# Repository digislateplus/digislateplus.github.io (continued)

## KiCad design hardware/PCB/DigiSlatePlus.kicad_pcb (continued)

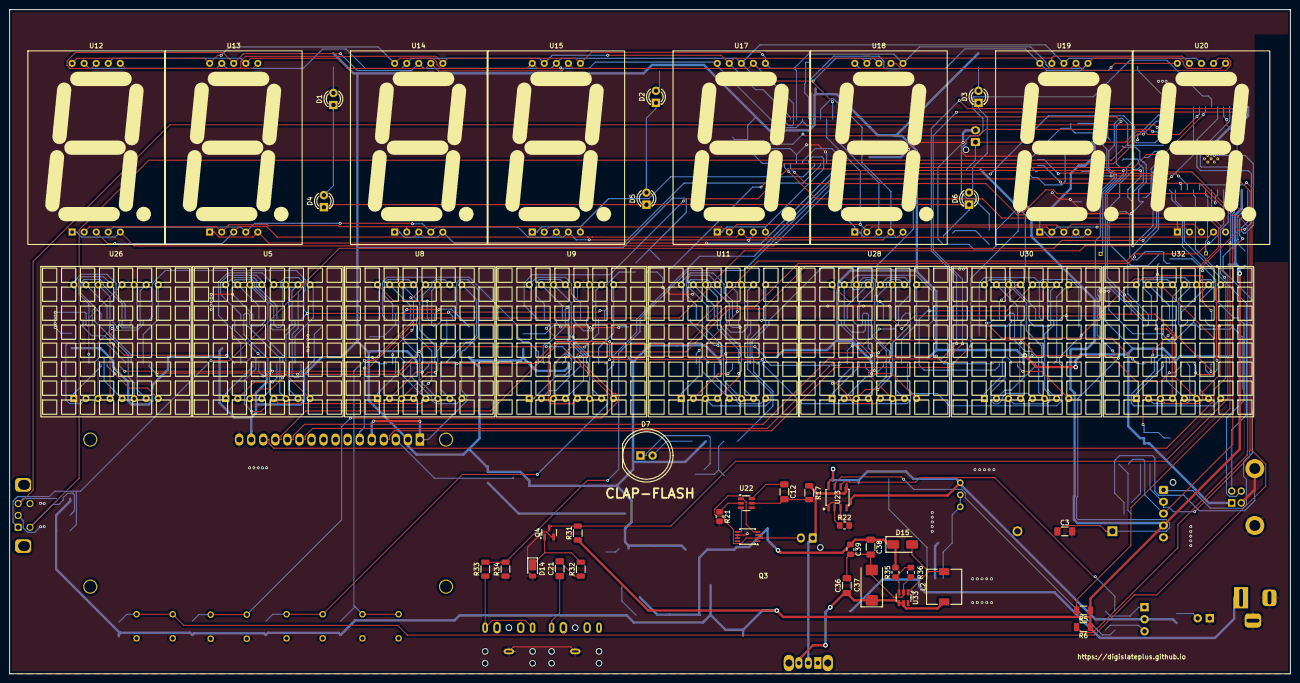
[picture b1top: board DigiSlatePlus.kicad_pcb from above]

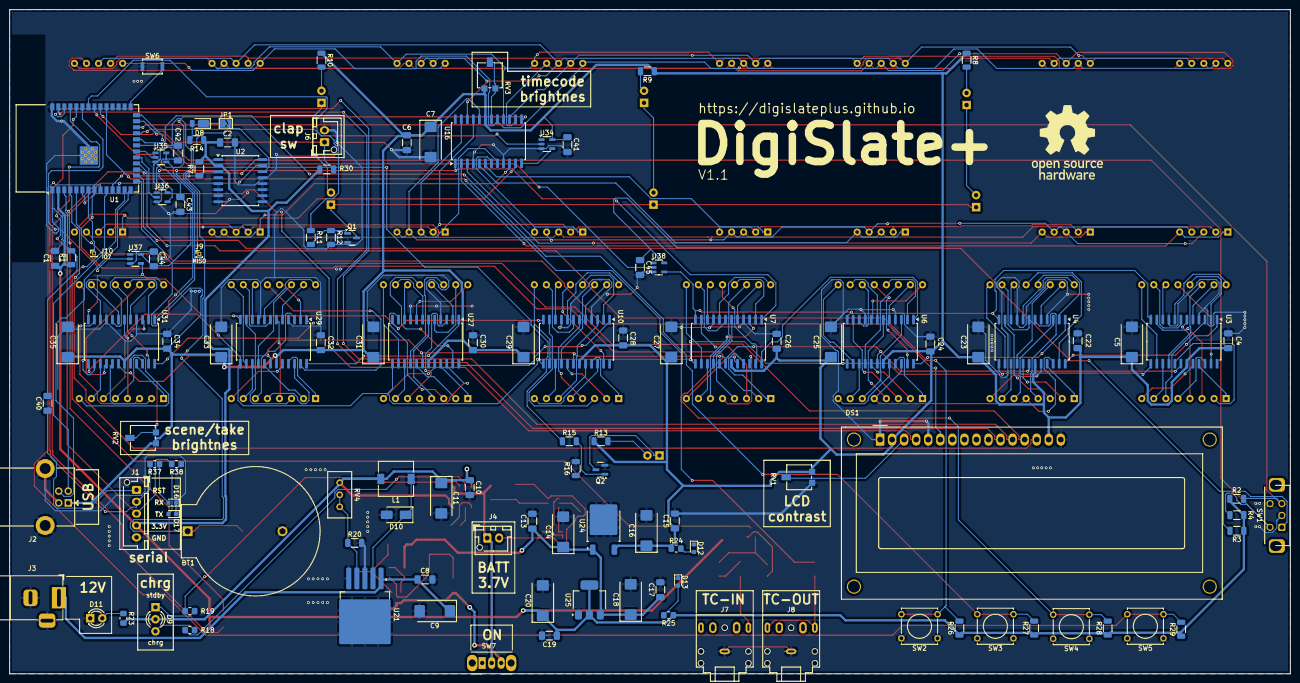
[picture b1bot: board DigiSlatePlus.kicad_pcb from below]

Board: 2 copper layers, 270.0 x 140.0 mm, 168 parts (119 on the bottom side), 238 nets.

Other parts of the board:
OHW-Logo: LOGO; Open-Source-Hardware-Logo

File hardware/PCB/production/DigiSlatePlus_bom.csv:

"Reference","Value","Datasheet","Footprint","Qty","DNP"
"BT1","Battery_Cell","~","battery holder:BatteryHolder_ComfortableElectronic_CH273-2450_1x2450","1",""
"C1,C2,C3,C4,C6,C12,C15,C19,C21,C22,C24,C26,C28,C30,C32,C34","100nF/50V","~","Capacitor_SMD:C_1206_3216Metric_Pad1.33x1.80mm_HandSolder","16",""
"C5,C7,C23,C25,C27,C29,C31,C33,C35","470uF/10V","~","Capacitor_Tantalum_SMD:CP_EIA-7343-31_Kemet-D_Pad2.25x2.55mm_HandSolder","9",""
"C8,C10,C13,C17","10nF/50V","~","Capacitor_SMD:C_1206_3216Metric_Pad1.33x1.80mm_HandSolder","4",""
"C9,C11","220uF/25V","~","Capacitor_Tantalum_SMD:CP_EIA-7343-31_Kemet-D_Pad2.25x2.55mm_HandSolder","2",""
"C14,C18","100uF/10V","~","Capacitor_Tantalum_SMD:CP_EIA-7343-31_Kemet-D_Pad2.25x2.55mm_HandSolder","2",""
"C16,C20","220uF/10V","~","Capacitor_Tantalum_SMD:CP_EIA-7343-31_Kemet-D_Pad2.25x2.55mm_HandSolder","2",""
"D1,D2,D3,D4,D5,D6,D7","LED","~","-- mixed values --","7",""
"D8,D14","1N4148","https://assets.nexperia.com/documents/data-sheet/1N4148_1N4448.pdf","Diode_SMD:D_PowerDI-123","2",""
"D9","LED_Dual_KAK","~","LED_THT:LED_D3.0mm-3","1",""
"D10","SS310","https://www.microdiode.com/uploadfiles//PDF/SS32-THRU-SS3200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","Diode_SMD:D_SMA","1",""
"D11","EXT","~","LED_THT:LED_D3.0mm","1",""
"D12","5V","~","LED_SMD:LED_0603_1608Metric","1",""
"D13","3V3","~","LED_SMD:LED_0603_1608Metric","1",""
"DS1","WC1602A","http://www.wincomlcd.com/pdf/WC1602A-SFYLYHTC06.pdf","Display:WC1602A","1",""
"J1","Serial","~","Connector_JST:JST_XH_B5B-XH-AM_1x05_P2.50mm_Vertical","1",""
"J2","USB_B","~","USB-B:USB_B_Lumberg_2411_02_Horizontal","1",""
"J3","+8-24 Volt","~","barrel jack:DC_Power_Jack_PCB_Mounted_2.1mm","1",""
"J4","Battery","~","Connector_JST:JST_XH_B2B-XH-AM_1x02_P2.50mm_Vertical","1",""
"J6","Mains","~","Connector_JST:JST_XH_B2B-XH-AM_1x02_P2.50mm_Vertical","1",""
"J7","Timecode IN","~","Connector_Audio:Jack_3.5mm_CUI_SJ1-3525N_Horizontal","1",""
"J8","Timecode OUT","~","Connector_Audio:Jack_3.5mm_CUI_SJ1-3525N_Horizontal","1",""
"J9","MISO","~","Connector_PinHeader_1.00mm:PinHeader_1x01_P1.00mm_Vertical","1",""
"J10","IO7","~","Connector_PinHeader_1.00mm:PinHeader_1x01_P1.00mm_Vertical","1",""
"JP1","charge","~","Jumper:SolderJumper-2_P1.3mm_Open_TrianglePad1.0x1.5mm","1",""
"L1","68uH","~","Inductor_SMD:L_7.3x7.3_H3.5","1",""
"Q1,Q2,Q4","2N2222","https://assets.nexperia.com/documents/data-sheet/MMBT2222A.pdf","Package_TO_SOT_SMD:SOT-23","3",""
"Q3","FS8205A","","Package_SO:TSSOP-8_3x3mm_P0.65mm","1",""
"R1,R2,R3,R4,R12,R16,R26,R27,R28,R29,R30,R32,RV4","10K","~","-- mixed values --","13",""
"R5,R6","4K7","~","Resistor_SMD:R_1206_3216Metric","2",""
"R7,R8,R9,R10","470R","~","Resistor_SMD:R_1206_3216Metric","4",""
"R11,R13,R15,R17,R31","100","~","Resistor_SMD:R_1206_3216Metric","5",""
"R14","220R","~","Resistor_SMD:R_1206_3216Metric","1",""
"R18,R19,R21","1K","~","Resistor_SMD:R_0805_2012Metric_Pad1.20x1.40mm_HandSolder","3",""
"R20","360R","~","Resistor_SMD:R_1206_3216Metric","1",""
"R22","1K2","~","Resistor_SMD:R_0805_2012Metric_Pad1.20x1.40mm_HandSolder","1",""
"R23,R24,R25","180","~","Resistor_SMD:R_0805_2012Metric_Pad1.20x1.40mm_HandSolder","3",""
"R33","1K8","~","Resistor_SMD:R_1206_3216Metric","1",""
"R34","5K6","~","Resistor_SMD:R_1206_3216Metric","1",""
"RV1,RV2,RV3","20K","~","Potentiometer_SMD:Potentiometer_Vishay_TS53YL_Vertical","3",""
"SW1","RotaryEncoder-SW","~","rotary:RotaryEncoder_Bourns_Horizontal","1",""
"SW2,SW3,SW4,SW5","1","~","Button_Switch_THT:SW_Tactile_Straight_KSA0Axx1LFTR","4",""
"SW6","BOOT","~","Button_Switch_SMD:SW_Push_SPST_NO_Alps_SKRK","1",""
"SW7","SW_DPDT_x2","~","Button_Switch_THT:SW_Slide_SPDT_Angled_CK_OS102011MA1Q","1",""
"U1","ESP32-S3-WROOM-1","https://www.espressif.com/sites/default/files/documentation/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","RF_Module:ESP32-S3-WROOM-1","1",""
"U2","DS3231M","http://datasheets.maximintegrated.com/en/ds/DS3231.pdf","Package_SO:SOIC-16W_7.5x10.3mm_P1.27mm","1",""
"U3,U4,U6,U7,U10,U16,U27,U29,U31","MAX7219","https://datasheets.maximintegrated.com/en/ds/MAX7219-MAX7221.pdf","Package_SO:SOIC-24W_7.5x15.4mm_P1.27mm","9",""
"U5,U8,U9,U11,U26,U28,U30,U32","~","https://www.tme.eu/Document/eeb740947eb2f07a796423aebfae2ea1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","FMY-12883:FMY-12883","8",""
"U12,U13,U14,U15,U17,U18,U19,U20","SA15-11SRWA","http://www.kingbrightusa.com/images/catalog/SPEC/SA15-11SRWA.pdf","7-segment-led:FYS-12011A","8",""
"U21","LM2596S-ADJ","http://www.ti.com/lit/ds/symlink/lm2596.pdf","Package_TO_SOT_SMD:TO-263-5_TabPin3","1",""
"U22","DW01A","https://hmsemi.com/downfile/DW01A.PDF","Package_TO_SOT_SMD:SOT-23-6","1",""
"U23","TP4056","TP4056-42-ESOP8","TP4056:TP4056-42-ESOP8_TPW","1",""
"U24","KA78M05_TO252","https://www.onsemi.com/pub/Collateral/MC78M00-D.PDF","Package_TO_SOT_SMD:TO-252-2","1",""
"U25","LD1117S33TR_SOT223","http://www.st.com/st-web-ui/static/active/en/resource/techni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","Package_TO_SOT_SMD:SOT-223-3_TabPin2","1",""

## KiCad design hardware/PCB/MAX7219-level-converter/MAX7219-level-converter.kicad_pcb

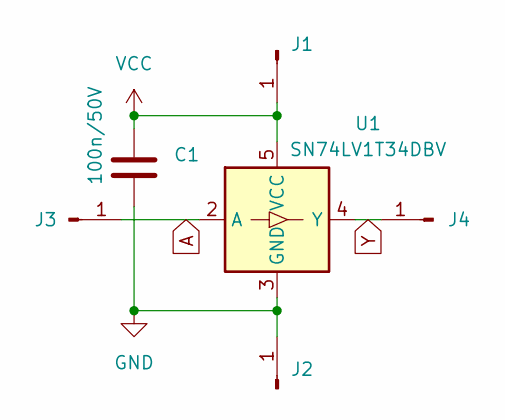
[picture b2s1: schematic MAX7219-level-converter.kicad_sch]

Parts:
C1: 100n/50V; C_0603_1608Metric_Pad1.08x0.95mm_HandSolder
J1: VCC; SolderWirePad_1x01_SMD_1x2mm
J2: GND; SolderWirePad_1x01_SMD_1x2mm
J3, J4: Conn_01x01_Pin; SolderWirePad_1x01_SMD_1x2mm
U1: SN74LV1T34DBV; SOT-23-5

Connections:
A: J3.1, U1.2 (A)
GND: C1.2, J2.1, U1.3 (GND)
VCC: C1.1, J1.1, U1.5 (VCC)
Y: J4.1, U1.4 (Y)

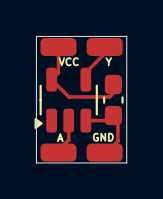
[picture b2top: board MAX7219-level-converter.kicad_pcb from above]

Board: 2 copper layers, 5.0 x 7.0 mm, 6 parts (0 on the bottom side), 4 nets.

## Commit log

2024-08-06 initial state
2024-08-06 changed file structure
2024-08-06 start Signed-off-by: Thomas Winkler <thomas.winkler@iggmp.net>
2024-08-06 README started
2024-08-08 Timecode output on BNC added userbit management added
2024-08-09 timecode generation stable version slate clapping button integrated for free run mode
2024-08-09 file cleanup
2024-08-09 bugfixes in timecode output
2024-08-09 output bit order correction stable output
2024-08-11 rtc synchronisation implemented
2024-08-11 slate function implemented bugfix in rtc-timecode synchronisation status display expanded
2024-08-12 hardware documentation added
2024-08-14 added documentation files
2024-08-14 KiCAD PCD design project added
2024-08-14 clean up folder structure
2024-08-14 PCD design added
2024-08-14 TP4056 library added
2024-08-18 KiCAD libraries added
2024-08-19 Schematic updated
2024-08-21 change page structure
2024-08-22 schematic and board layout finished
2024-08-22 first finished schematic version
2024-08-26 Rename function.md to doc/function.md
2024-08-26 Rename hardware.md to doc/hardware.md
2024-08-26 Rename _config.yml to doc/_config.yml
2024-08-26 Rename README.md to README.md
2024-08-26 Rename _config.yml to _config.yml
2024-08-26 Rename function.md to function.md
2024-08-26 Rename hardware.md to hardware.md
2024-08-28 Rename hardware/Bill of materials.md to hardware/DigiSlate - original/Bill of materials.md
2024-08-28 Rename hardware/DigiSlate - original/Bill of materials.md to hardware/DigiSlate - original/DigiSlate - original/Bill of materials.md
2024-08-28 Rename hardware/DigiSlate - original/DigiSlate - original/Bill of materials.md to hardware/DigiSlate - original/Bill of materials.md
2024-08-28 Rename hardware/Bill Of Material.pdf to hardware/DigiSlate - original/Bill Of Material.pdf
2024-08-29 readme updated
2024-08-29 reader class
2024-08-30 reader class initial state
2024-09-05 final 1.0 board version
2024-09-09 bugfixes in board
2024-09-11 change to dot matrix led display
2024-09-11 dot matrix bugfixes
2024-09-12 added KiCad libraries schematic bugfixes
2024-09-13 first 1.0 board version
2024-09-13 minor bugfixes in schematics and board
2024-09-13 position data added
2024-09-14 production data added
2024-09-14 work on read method
2024-09-15 reader method first reading status getting framerate not verified
2024-09-15 jam mode to write the timecode from the input to thr rtc added frame offset is still missing
2024-09-16 bom added
2024-09-16 add eeprom class
2024-09-18 modified kikad project
2024-09-23 add settings class
2024-09-24 add button class
2024-09-24 add button class to settings class
2024-09-27 new harware bugfixes while building the prototype
2024-09-29 initial ESP32 version
2024-09-29 KiCAD bagfix update
2024-10-04 KiCAD library MAX7219 added LED driver library updated to access multiple controllers
2024-10-07 level converter added to schematic and pcb
2024-10-07 capacitors added to signal level converters
2024-10-08 signal level converter for new hardware version 1.0
2024-10-08 level converter KiCad project added
2024-10-08 minor fixes on pcb
2024-10-20 class for matrix led display begun charset.h with font for matrix display finished
2024-10-20 missing GND connection to MAX7219 added
2024-10-24 working matrix display
2024-10-24 print character
2025-07-01 Last bug fixes
2025-07-01 scene class added bugfixes
2025-07-01 Assembly PDF added
2025-07-02 Rename ToDos.md to todos.md
